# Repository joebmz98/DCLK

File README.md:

# DCLK — Dual MIDI Clock

**.axs instruments** · Firmware v1.6.3 · Hardware v1.0

DCLK is a dual MIDI clock built around an STM32F411 Black Pill. It sends
MIDI clock to two TRS (Type A) outputs and over USB MIDI, with quantised
start/stop and a separate clock divider for each output, so two machines can
be dropped in and out of a jam on the bar.

## Update the firmware

### ➜ [DCLK Web Flasher & Editor](https://joebmz98.github.io/DCLK-Flasher/)

Flash the latest release straight from Chrome or Edge on a computer. No
software to install. Your saved settings are kept. Flasher source:
[DCLK-Flasher](https://github.com/joebmz98/DCLK-Flasher).

1. Plug DCLK into the computer with a USB‑C data cable.
2. Put DCLK into update mode: click **Enter update mode** on the flasher,
   or choose **Settings > UPDATE** and push the encoder. The screen shows
   **DFU READY**. (Firmware 1.5 and later. On older firmware, or if DCLK
   won't start: hold **BOOT0**, tap **NRST**, keep holding BOOT0 for about a
   second. The screen and LEDs stay off in that mode.)
3. Click **Flash Firmware** and choose **STM32 BOOTLOADER**.

Windows needs a one-time WinUSB driver (Zadig); the flasher's Troubleshooting
section walks through it.

## Features

- Tempo from 30 to 300 BPM, set with the encoder (24 PPQN)
- Two TRS Type A MIDI outputs plus USB MIDI (class compliant, shows up as
  **DCLK**, no drivers)
- Quantised start: outputs wait for the next bar boundary of the wait length
  (1, 2, 4, 8 or 16 bars) before sending Start
- Optional quantised stop, landing on the same boundary
- Per-output clock divide: /1 /2 /3 /4 /6 /8
- USB MIDI clock follows either output
- Two 5 V analogue sync outputs (3.5 mm TRS): clock pulse on the tip
  (1, 2, 4, 8, 12 or 24 PPQN per output, default 24, after the channel's
  divider), run gate on the ring. SYNC 1 follows CH1, SYNC 2 follows CH2
  (firmware 1.6 and later; PPQN setting from 1.6.1)
- Screen saver: dims while a clock runs, switches off when stopped, with a
  slow breathing BEAT LED in standby
- Capacitive touch buttons (CAP1206) for CH1, CH2 and Settings
- Settings saved to flash and kept across power cycles and firmware updates

## Using DCLK

| Control | Action |
| --- | --- |
| Encoder (main screen) | Set tempo |
| **CH1** / **CH2** | Start or stop that output. Press again while waiting to cancel |
| **Settings** | Open the menu · back · cancel an edit |
| Encoder push | Select / confirm in the menu |

Clock, Start and Stop are MIDI System Real-Time messages, so they carry no
MIDI channel: "CH1" and "CH2" mean the two output jacks.

**LEDs**

- **CH1 / CH2:** solid while running, slow fade while waiting to start, blink
  on the beat while waiting for a quantised stop, off when stopped.
- **BEAT:** flashes on every beat.

**Main screen:** a white CH1 / CH2 tab appears along the top while that
output plays, and disappears when it stops (firmware 1.6.2 and later). Below them
are the tempo and four beat bars; the current beat stands taller. The bars
and the BEAT LED move while an output plays, and (from 1.6.3) while a USB
host plays in HOST mode even with both outputs off.

**Menus**

| Menu | Settings |
| --- | --- |
| LEDS | Brightness: LO / MID / HI |
| MIDI | WAIT LEN · STOP Q · CH1 DIV · CH2 DIV · USB OUT |
| SYNC | SYNC 1 / SYNC 2 pulses per quarter note: 1 / 2 / 4 / 8 / 12 / 24 |
| SCREEN | SAVER: OFF / 1 / 5 / 10 / 30 min |
| MONITOR | USB and clock diagnostics; encoder push toggles a USB test note (C4, ch 1) |
| UPDATE | Restart into DFU mode for the web flasher (push the encoder to confirm, SETTINGS cancels) |
| ABOUT | Product, maker and firmware version |

## Connections

| Connector | Use |
| --- | --- |
| USB‑C (Black Pill) | USB MIDI clock, power, firmware updates |
| MIDI OUT 1 / 2 | 3.5 mm TRS, Type A |
| SYNC OUT 1 / 2 | 3.5 mm TRS, 5 V: tip = clock pulse, ring = run gate (high while playing) |
| DC jack | 5 V, centre positive |

## Hardware

KiCad 9 project in `build/DCLK-MIDI-Clock/`, with JLCPCB-ready Gerbers,
BOM and placement files in `production/`. Custom footprints are in
`lib/DCLK.pretty/`.

Main parts: STM32F411CEU6 Black Pill, SSD1306 128×32 I²C OLED, CAP1206
touch controller, Alps EC11E encoder with switch, 2× CUI SJ1‑3525N TRS jacks,
GCT DCJ200 DC jack, 3× 5 mm LEDs.

| Function | Pin |
| --- | --- |
| MIDI OUT 1 / 2 (TX) | PA9 (USART1) / PA2 (USART2) |
| SYNC 1 clock / run | PA8 / PB15 (via 74AHCT125 to 5 V) |
| SYNC 2 clock / run | PA5 / PA4 (via 74AHCT125 to 5 V) |
| CH1 / CH2 / Settings touch pads | CAP1206 CS1 / CS2 / CS3 (I²C 0x28) |
| CAP1206 ALERT# | PB12 |
| Encoder A / B / push | PB4 / PB5 / PB13 |
| LED CH1 / CH2 / BEAT | PB8 / PB9 / PA6 (PWM) |
| OLED + CAP1206 SDA / SCL | PB7 / PB6 |

## Building the firmware

The sketch is `src/dclk_midi_clock/dclk_midi_clock.ino` (Arduino IDE).

- **Core:** STM32duino with the custom board entry
  **DCLK Dual MIDI Clock**, which gives a clean 48 MHz USB clock from the
  Black Pill's 25 MHz crystal. The sketch warns at compile time if another
  board is selected.
- **Board options:** USB support *None* (TinyUSB provides USB) · U(S)ART
  support *Enabled (generic 'Serial')*.
- **Libraries:** Adafruit GFX, Adafruit SSD1306, Adafruit TinyUSB.
- **Upload method:** STM32CubeProgrammer (DFU or SWD). The image must be
  linked at `0x08000000`, with no HID or UF2 bootloader offset.

To publish a release, use **Sketch > Export Compiled Binary**, copy the
`.hex` into the flasher repo's `firmware/` folder and update its
`manifest.json`.

## Repository layout

```
src/dclk_midi_clock/   firmware sketch, compiled builds, font
legacy/                every firmware release (hex, bin, source)
build/DCLK-MIDI-Clock/ KiCad project and production files
lib/DCLK.pretty/       custom footprints
assets/                artwork (polarity marking)
```

## License

MIT. See [LICENSE](LICENSE). © 2026 .axs instruments

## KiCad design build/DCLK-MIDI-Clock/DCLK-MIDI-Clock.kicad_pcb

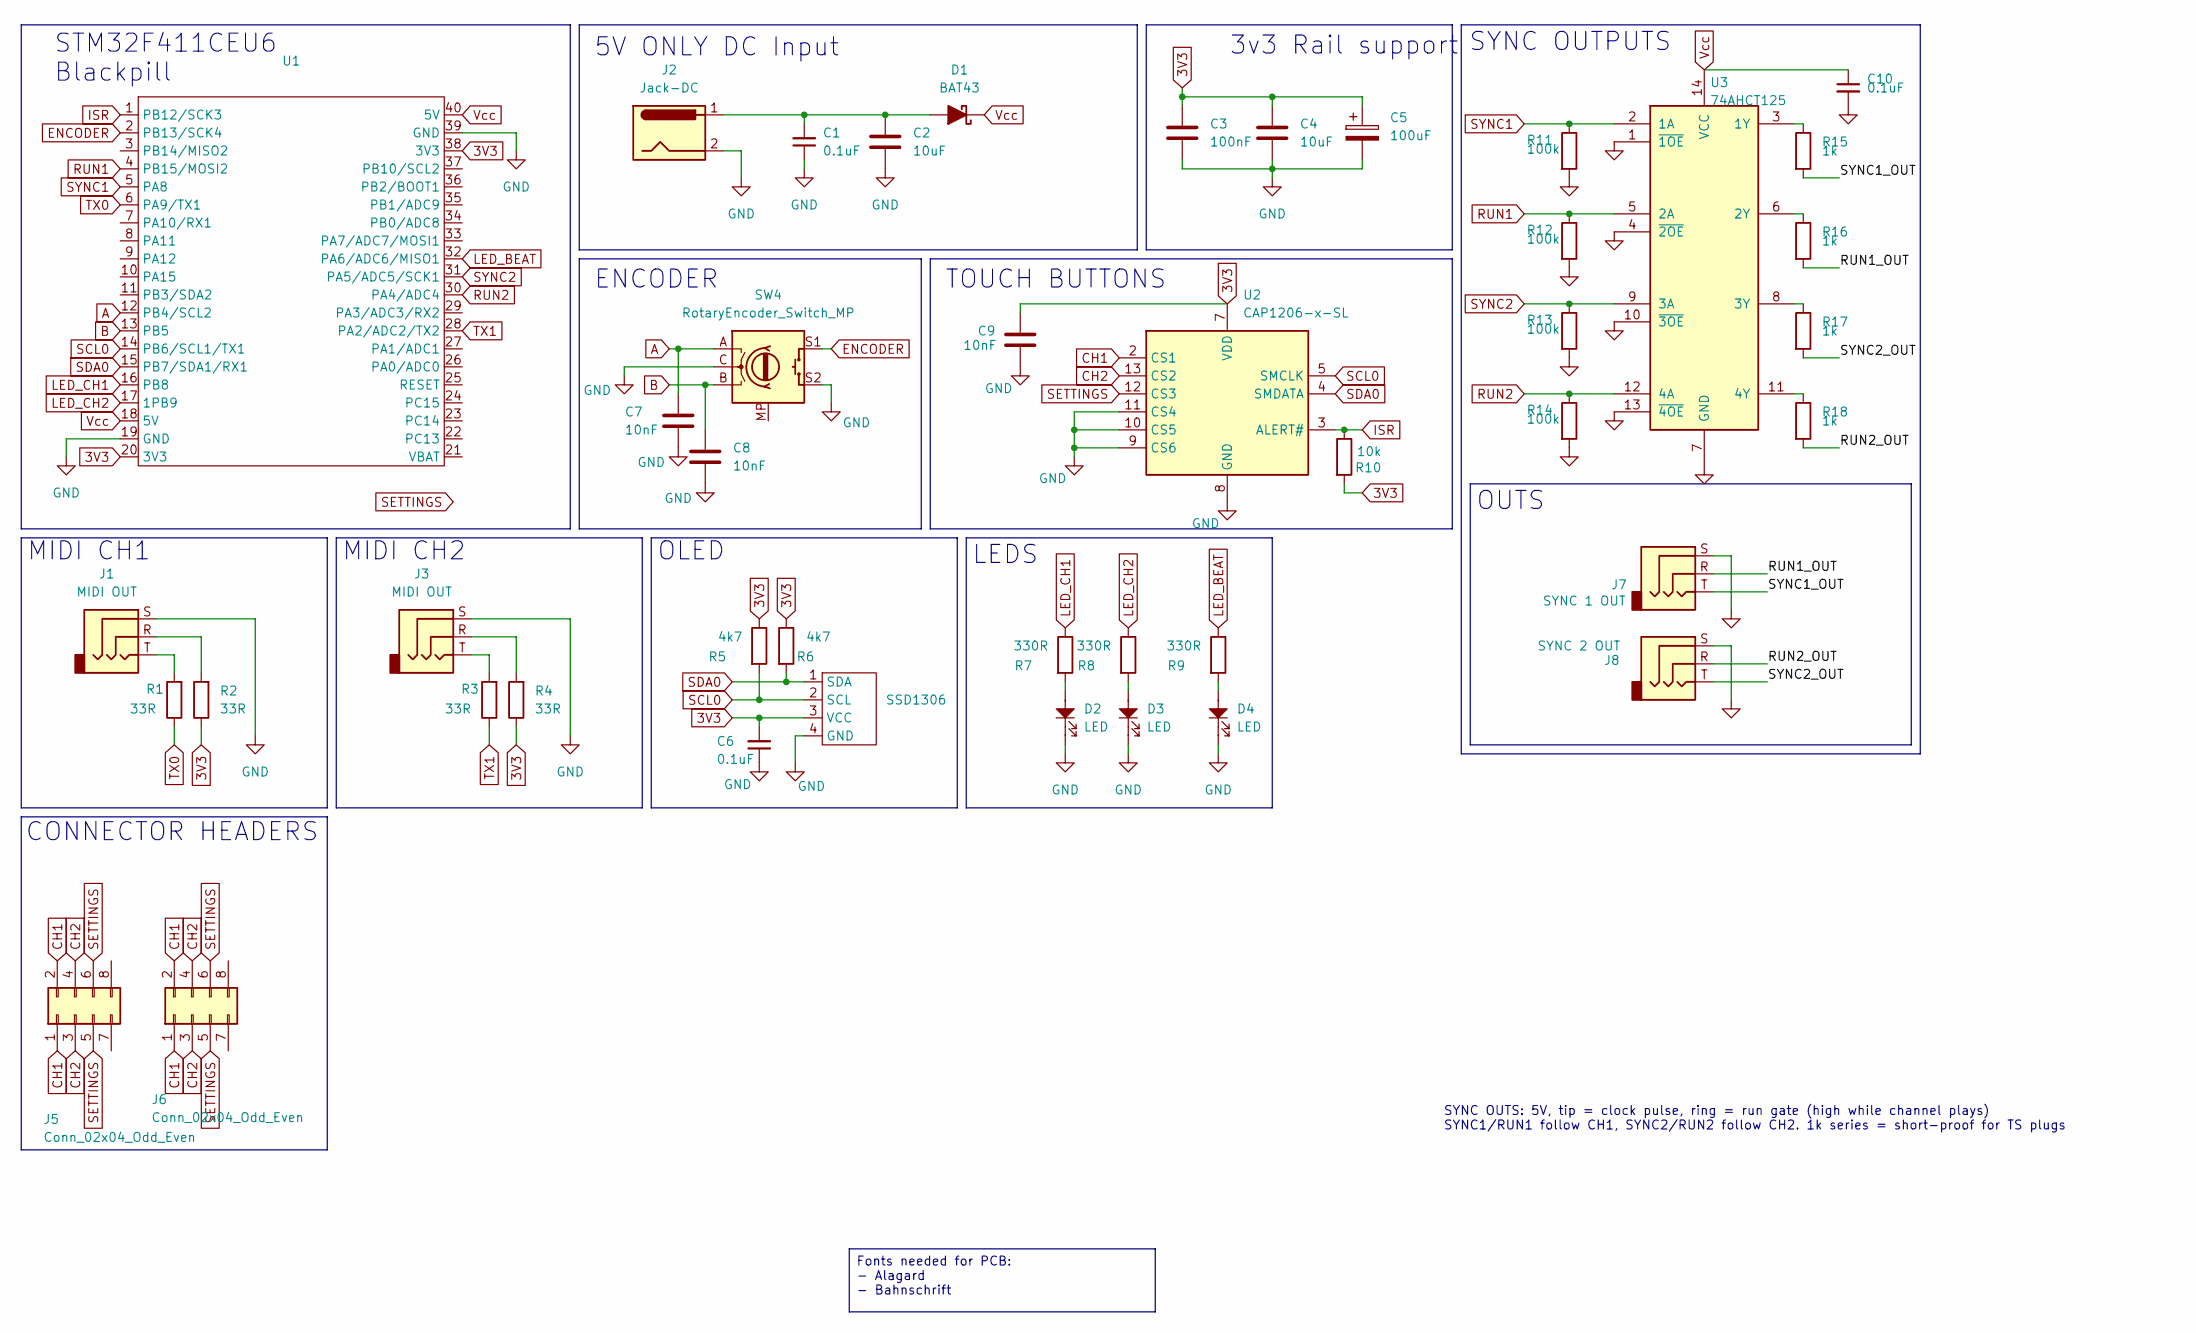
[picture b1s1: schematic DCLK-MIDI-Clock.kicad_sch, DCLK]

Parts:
C1, C6, C10: 100nF; C_1206_3216Metric; LCSC Part # C24497
C2, C4: 10uF; C_1206_3216Metric_Pad1.33x1.80mm_HandSolder; LCSC Part # C13585
C3: 100nF; C_1206_3216Metric_Pad1.33x1.80mm_HandSolder; LCSC Part # C24497
C5: 100uF; CP_Radial_D4.0mm_P1.50mm
C7, C8, C9: 10nF; C_1206_3216Metric_Pad1.33x1.80mm_HandSolder; LCSC Part # C1846
D1: BAT43; D_SOD-123; LCSC Part # C19167
D2, D3, D4: LED; LED_D5.0mm
J1, J3: MIDI OUT; Jack_3.5mm_CUI_SJ1-3525N_Horizontal_edit
J2: Jack-DC; BarrelJack_GCT_DCJ200-10-A_Horizontal
J5: Conn_02x04_Odd_Even; PinSocket_2x04_P2.54mm_Vertical; LCSC Part # C54907661
J6: Conn_02x04_Odd_Even; PinHeader_2x04_P2.54mm_Vertical_SMD; LCSC Part # C41397153
J7: SYNC 1 OUT; PJ307-TRS-SOCKET
J8: SYNC 2 OUT; PJ307-TRS-SOCKET
R1, R2, R3, R4: 33R; R_0603; LCSC Part # C23140
R5, R6: 4k7; R_0603; LCSC Part # C23162
R7, R8, R9: 330R; R_0603; LCSC Part # C22104
R10: 10k; R_0603; LCSC Part # C15401
R11, R12, R13, R14: 100k; R_0402_1005Metric; LCSC Part # C25530
R15, R16, R17, R18: 1k; R_0402_1005Metric; LCSC Part # C11702
SSD1306: SSD1306-128x32
SW4: RotaryEncoder_Switch_MP; RotaryEncoder_Alps_EC11E-Switch_Vertical_H20mm_MountingHoles
U1: Z_module_black_pill_STM32F411
U2: CAP1206-x-SL; SOIC-14_3.9x8.7mm_P1.27mm; LCSC Part # C2652106
U3: 74AHCT125; SOIC-14_3.9x8.7mm_P1.27mm; LCSC Part # C155176

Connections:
3V3: C3.1, C4.1, C5.1, C6.2, C9.2, R2.1, R4.1, R5.1, R6.1, R10.2, SSD1306.3 (VCC), U1.20 (3V3), U1.38 (3V3), U2.7 (VDD)
/RUN1_OUT: J7.R, R16.2
/RUN2_OUT: J8.R, R18.2
/SYNC1_OUT: J7.T, R15.2
/SYNC2_OUT: J8.T, R17.2
A: C7.1, SW4.A, U1.12 (PB4/SCL2)
B: C8.1, SW4.B, U1.13 (PB5)
CH1: J5.1, J5.2, J6.1, J6.2, U2.2 (CS1)
CH2: J5.3, J5.4, J6.3, J6.4, U2.13 (CS2)
ENCODER: SW4.S1, U1.2 (PB13/SCK4)
GND: C1.1, C2.2, C3.2, C4.2, C5.2, C6.1, C7.2, C8.2, C9.1, C10.2, D2.1, D3.1, D4.1, J1.S, J2.2, J3.S, J7.S, J8.S, R11.2, R12.2, R13.2, R14.2, SSD1306.4 (GND), SW4.C, SW4.S2, U1.19 (GND), U1.39 (GND), U2.8 (GND), U2.9 (CS6), U2.10 (CS5), U2.11 (CS4), U3.1 (~1OE), U3.4 (~2OE), U3.7 (GND), U3.10 (~3OE), U3.13 (~4OE)
ISR: R10.1, U1.1 (PB12/SCK3), U2.3 (ALERT#)
LED_BEAT: R9.1, U1.32 (PA6/ADC6/MISO1)
LED_CH1: R7.1, U1.16 (PB8)
LED_CH2: R8.1, U1.17 (1PB9)
unnamed: C1.2, C2.1, D1.2 (A), J2.1
unnamed: D2.2, R7.2
unnamed: D3.2, R8.2
unnamed: D4.2, R9.2
unnamed: J1.R, R2.2
unnamed: J1.T, R1.2
unnamed: J3.R, R4.2
unnamed: J3.T, R3.2
unnamed: R15.1, U3.3 (1Y)
unnamed: R16.1, U3.6 (2Y)
unnamed: R17.1, U3.8 (3Y)
unnamed: R18.1, U3.11 (4Y)
RUN1: R12.1, U1.4 (PB15/MOSI2), U3.5 (2A)
RUN2: R14.1, U1.30 (PA4/ADC4), U3.12 (4A)
SCL0: R5.2, SSD1306.2 (SCL), U1.14 (PB6/SCL1/TX1), U2.5 (SMCLK)
SDA0: R6.2, SSD1306.1 (SDA), U1.15 (PB7/SDA1/RX1), U2.4 (SMDATA)
SETTINGS: J5.5, J5.6, J6.5, J6.6, U2.12 (CS3)
SYNC1: R11.1, U1.5 (PA8), U3.2 (1A)
SYNC2: R13.1, U1.31 (PA5/ADC5/SCK1), U3.9 (3A)
TX0: R1.1, U1.6 (PA9/TX1)
TX1: R3.1, U1.28 (PA2/ADC2/TX2)
Vcc: C10.1, D1.1 (K), U1.18 (5V), U1.40 (5V), U3.14 (VCC)

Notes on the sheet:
SYNC OUTS: 5V, tip = clock pulse, ring = run gate (high while channel plays) SYNC1/RUN1 follow CH1, SYNC2/RUN2 follow CH2. 1k series = short-proof for TS plugs
OUTS
STM32F411CEU6 Blackpill
5V ONLY DC Input
TOUCH BUTTONS
3v3 Rail support
ENCODER
MIDI CH2
SYNC OUTPUTS
LEDS
MIDI CH1
CONNECTOR HEADERS
OLED
Fonts needed for PCB: - Alagard - Bahnschrift

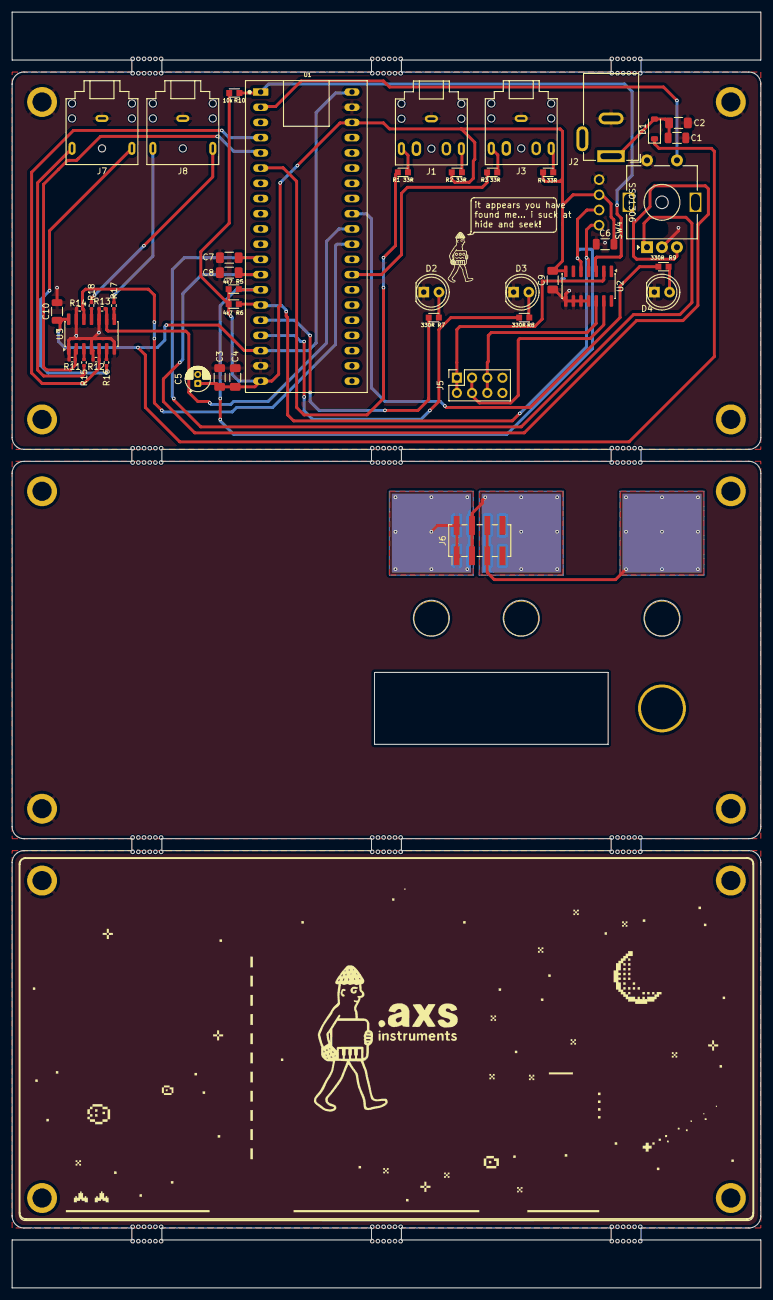
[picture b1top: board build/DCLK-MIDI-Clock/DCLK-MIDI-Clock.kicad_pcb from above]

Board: 2 copper layers, 125.0 x 213.0 mm, 56 parts (0 on the bottom side), 37 nets.

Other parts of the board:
MB**: MouseBite_Tab; MouseBite_Tab_5mm_Gap2mm
MB**#2, MB**#3, MB**#4, MB**#5, MB**#6, MB**#7, MB**#8, MB**#9, MB**#10, MB**#11, MB**#12: MouseBite_Tab; MouseBite_Tab_5mm_Gap2mm

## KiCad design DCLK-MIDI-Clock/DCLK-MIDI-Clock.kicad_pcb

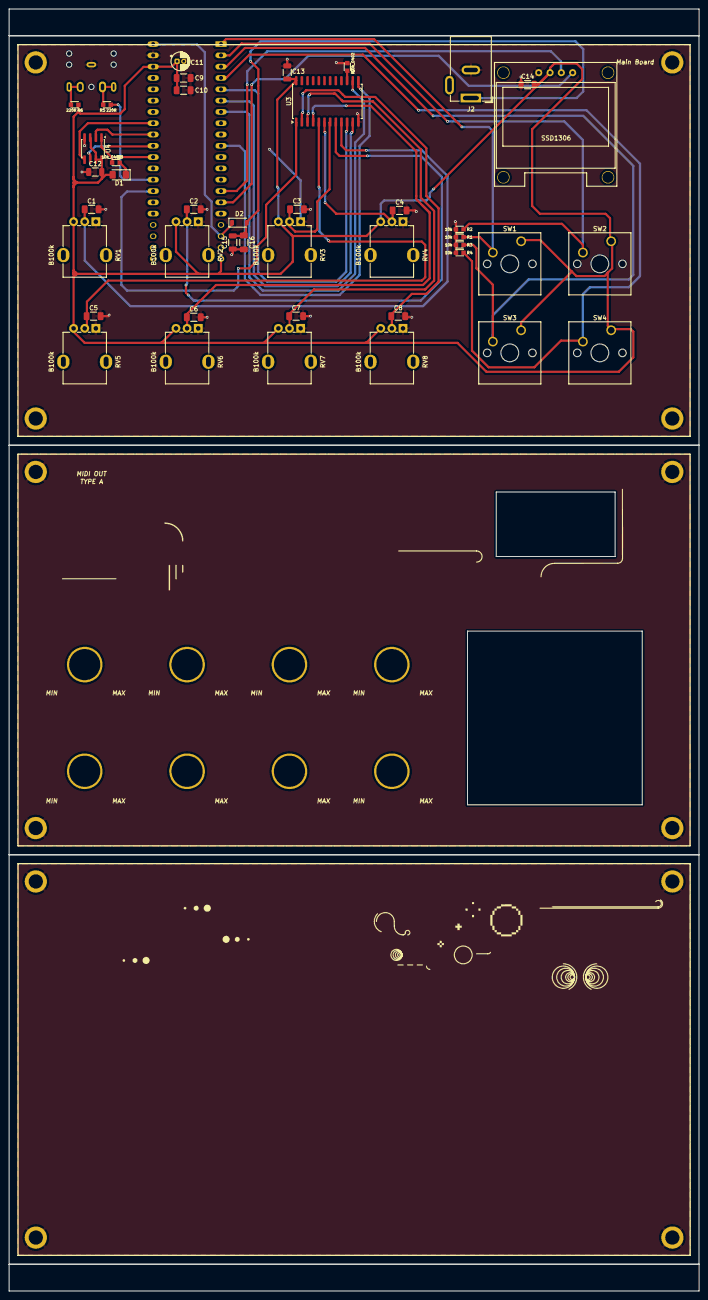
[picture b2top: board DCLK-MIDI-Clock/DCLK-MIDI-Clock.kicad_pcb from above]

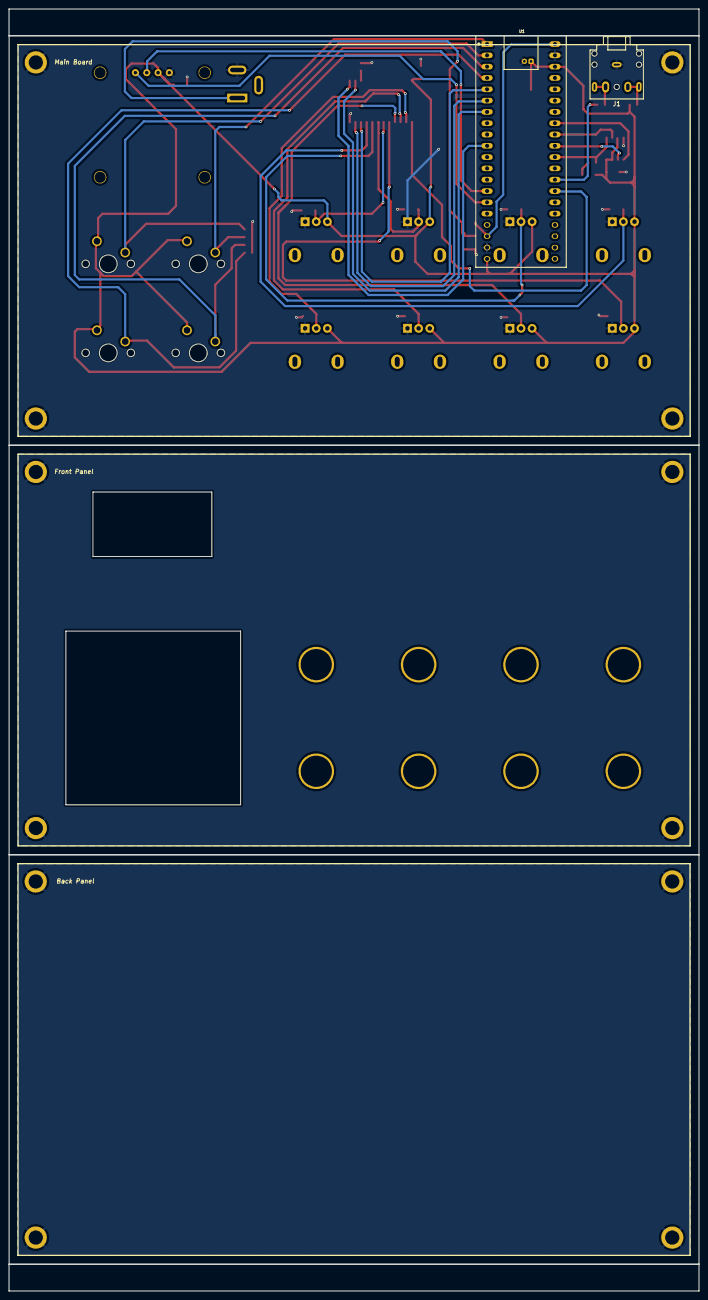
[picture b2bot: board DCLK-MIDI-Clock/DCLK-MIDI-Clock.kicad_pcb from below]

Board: 2 copper layers, 155.0 x 288.0 mm, 44 parts (3 on the bottom side), 32 nets.

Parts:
C1, C2, C3, C4, C5, C6, C7, C8: C_Generic; C_1206_3216Metric_Pad1.33x1.80mm_HandSolder
C9: 100nF; C_1206_3216Metric_Pad1.33x1.80mm_HandSolder
C10, C16: 10uF; C_1206_3216Metric_Pad1.33x1.80mm_HandSolder
C11: 100uF; CP_Radial_D4.0mm_P1.50mm
C12, C13, C14, C15: 100nF_0603_16V; C_1206_3216Metric
D1: LED; LED_1206_3216Metric_Pad1.42x1.75mm_HandSolder
D2: BAT43; D_SOD-123
J1: MIDI OUT; Jack_3.5mm_CUI_SJ1-3525N_Horizontal_edit
J2: Jack-DC; BarrelJack_GCT_DCJ200-10-A_Horizontal
R1, R2, R3, R4: 10k; R_0603
R5, R6: 220R; R_0603
R7, R8: 10k_0402; R_0603
RV1, RV2, RV3, RV4, RV5, RV6, RV7, RV8: B100k; Potentiometer_RV09_BigPads
SSD1306: SSD1306_OLED_Module
SW1: ASSIGN; SW_Cherry_MX_1.00u_PCB
SW2: ENTER; SW_Cherry_MX_1.00u_PCB
SW3: PREV; SW_Cherry_MX_1.00u_PCB
SW4: NEXT; SW_Cherry_MX_1.00u_PCB
U1: Z_module_black_pill_STM32F411
U3: CD74HC4067M; SOIC-24W_7.5x15.4mm_P1.27mm
U4: W25Q64; SOIC-8_3.9x4.9mm_P1.27mm

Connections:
3V3: C9.1, C10.1, C11.1, C12.2, C13.1, C14.2, D1.2 (A), R6.1, RV1.3, RV2.3, RV3.3, RV4.3, RV5.3, RV6.3, RV7.3, RV8.3, SSD1306.3 (VCC), SW1.1 (A), SW2.1 (A), SW3.1 (A), SW4.1 (A), U1.20 (3V3), U1.38 (3V3), U3.24 (VCC), U4.3 (WP), U4.7 (HOLD), U4.8 (VCC)
ASSIGN: R1.1, SW1.2 (B), U1.1 (PB12/SCK3)
CLK: U1.31 (PA5/ADC5/SCK1), U4.6 (CLK)
CS: R8.1, U1.30 (PA4/ADC4), U4.1 (CS)
ENTER: R2.1, SW2.2 (B), U1.2 (PB13/SCK4)
GND: C1.2, C2.2, C3.2, C4.2, C5.2, C6.2, C7.2, C8.2, C9.2, C10.2, C11.2, C12.1, C13.2, C14.1, C15.1, C16.2, J1.S, J2.2, R1.2, R2.2, R3.2, R4.2, R7.2, RV1.1, RV2.1, RV3.1, RV4.1, RV5.1, RV6.1, RV7.1, RV8.1, SSD1306.4 (GND), U1.19 (GND), U1.39 (GND), U3.12 (GND), U4.4 (GND)
MISO: U1.32 (PA6/ADC6/MISO1), U4.2 (MISO/DO)
MOSI: U1.33 (PA7/ADC7/MOSI1), U4.5 (MOSI/DI)
NEXT: R4.1, SW4.2 (B), U1.4 (PB15/MOSI2)
unnamed: D1.1 (K), R8.2
unnamed: C15.2, C16.1, D2.2 (A), J2.1
unnamed: J1.R, R6.2
unnamed: J1.T, R5.2
unnamed: R7.1, U3.15 (~E)
PREV: R3.1, SW3.2 (B), U1.3 (PB14/MISO2)
S0: U1.5 (PA8), U3.10 (S0)
S1: U1.6 (PA9/TX1), U3.11 (S1)
S2: U1.7 (PA10/RX1), U3.14 (S2)
S3: U1.10 (PA15), U3.13 (S3)
SCL0: SSD1306.2 (SCL), U1.14 (PB6/SCL1/TX1)
SDA0: SSD1306.1 (SDA), U1.15 (PB7/SDA1/RX1)
SIG: U1.27 (PA1/ADC1), U3.1 (COM)
TX0: R5.1, U1.28 (PA2/ADC2/TX2)
Vcc: D2.1 (K), U1.18 (5V), U1.40 (5V)
pot1: C1.1, RV1.2, U3.9 (I0)
pot2: C2.1, RV2.2, U3.8 (I1)
pot3: C3.1, RV3.2, U3.7 (I2)
pot4: C4.1, RV4.2, U3.6 (I3)
pot5: C5.1, RV5.2, U3.5 (I4)
pot6: C6.1, RV6.2, U3.4 (I5)
pot7: C7.1, RV7.2, U3.3 (I6)
pot8: C8.1, RV8.2, U3.2 (I7)

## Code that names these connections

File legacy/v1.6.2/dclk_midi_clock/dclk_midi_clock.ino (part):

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//
// CH1, CH2 and SETTINGS are capacitive touch pads read by a CAP1206
// (CS1 = CH1, CS2 = CH2, CS3 = SETTINGS) on the same I2C bus as the OLED,
// with its ALERT# line on PB12. The encoder and its push switch are wired
// straight to the BlackPill (PB4 / PB5 / PB13).
//
// SYNC OUTPUTS (v1.6+): two 3.5 mm TRS jacks, buffered to 5 V by a 74AHCT125.
//   Tip  = clock pulse, SYNC n PPQN setting per quarter note (after the
//          channel's clock divider), SYNC_PULSE_US wide
//   Ring = run gate, high while that channel is playing
//   SYNC 1 follows CH1 (PA8 tip, PB15 ring), SYNC 2 follows CH2 (PA5 tip,
//   PA4 ring). Pulse ends are timed by TIM5.
// ********************* //

// ********************* //
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constexpr uint8_t N_LED_LEVELS = sizeof(led_levels) / sizeof(led_levels[0]);

// ---------- Pins ----------
constexpr uint8_t PIN_ENC_A = PB4, PIN_ENC_B = PB5;
constexpr int8_t  ENC_DIR     = -1;         // +1 / -1: flips the encoder's direction everywhere
constexpr uint8_t PIN_ENC_BTN = PB13;       // encoder shaft push button
constexpr uint8_t PIN_TOUCH_ALERT = PB12;   // CAP1206 ALERT# (open drain, active low, R10 pull-up)

constexpr uint8_t PIN_LED_BEAT = PA6;                // TIM3_CH1 PWM
constexpr uint8_t PIN_LED_STATUS[2] = { PB8, PB9 };  // TIM4 PWM

HardwareSerial MidiOut1(PA10, PA9);  // USART1 (RX unused)
HardwareSerial MidiOut2(PA3, PA2);   // USART2 (RX unused)
HardwareSerial* midi[2] = { &MidiOut1, &MidiOut2 };

Adafruit_SSD1306 display(128, 32, &Wire, -1);
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volatile uint8_t usb_tx_tail = 0;

// Diagnostics (shown on the DIAG screen)
volatile uint32_t usb_ring_drops = 0;   // ISR found ring full
uint32_t usb_pkts_sent  = 0;            // packets accepted by TinyUSB
uint32_t usb_pkts_retry = 0;            // TinyUSB FIFO full, retried later

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  ABOUT
};
Screen  screen        = Screen::MAIN;
uint8_t menu_sel      = 0;     // SETTINGS: 0=LEDS 1=MIDI 2=SCREEN
uint8_t midi_menu_sel = 0;
uint8_t sync_menu_sel = 0;     // SYNC: 0 = SYNC 1, 1 = SYNC 2
uint8_t edit_idx      = 0;     // option index being edited (MIDI_EDIT / SAVER_EDIT)
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      display.fillRect(i * bar_w + 2, (i == b) ? 31 : 28, bar_w - 4, 4, SSD1306_WHITE);
    }
    display.display();
    analogWrite(PIN_LED_BEAT, b == 0 ? 255 : 140);
    delay(60);
    analogWrite(PIN_LED_BEAT, 0);
    delay(90);
  }

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}

void touchService() {
  static uint8_t  prev       = 0;
  static uint32_t last_poll  = 0;
  static uint32_t last_retry = 0;
  const uint32_t now = millis();
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    if (now - last_retry < TOUCH_RETRY_MS) return;
    last_retry = now;
    touch_ok = capInit();
    prev = 0;
    if (screen == Screen::DIAG) ui_dirty = true;
    return;
  }
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    return;
  }

  const uint8_t pressed = latched & TOUCH_MASK & ~prev;
  prev = current & TOUCH_MASK;

  if (pressed & TOUCH_CH1)      onOutputButton(0);
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    uint16_t peak = (uint16_t)led_base + led_flash;
    if (peak > 255) peak = 255;
    uint8_t beat_duty = (uint32_t)peak * (PPQN - 1 - phase) / (PPQN - 1);
    analogWrite(PIN_LED_BEAT, beat_duty);
  } else if (screen_asleep && !pending[0] && !pending[1]) {
    // Standby: soft breathe, one cycle per bar at the current tempo
    uint32_t period = 240000UL / bpm;                 // 4 beats in ms
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    uint32_t tri    = (pt < half) ? (pt * 255 / half) : ((period - pt) * 255 / half);
    uint16_t peak   = led_base / 3;
    if (peak < 8) peak = 8;                           // still visible at low LED setting
    analogWrite(PIN_LED_BEAT, (uint8_t)(((tri * tri) / 255) * peak / 255));
  } else {
    analogWrite(PIN_LED_BEAT, 0);
  }

  uint8_t flash = 0;
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  MidiOut1.flush();
  MidiOut2.flush();

  analogWrite(PIN_LED_BEAT,      0);
  analogWrite(PIN_LED_STATUS[0], 0);
  analogWrite(PIN_LED_STATUS[1], 0);

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    NVIC->ICPR[i] = 0xFFFFFFFF;
  }

  // PA10 is USART1_RX, which the bootloader also listens on. MIDI OUT 1
  // leaves it unconnected, and noise there can make the bootloader choose
  // the serial port instead of USB. Hold it high with the internal pull-up.
  __HAL_RCC_GPIOA_CLK_ENABLE();
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    digitalWriteFast(RUN_PIN[i],  LOW);
  }

  pinMode(PIN_LED_BEAT, OUTPUT);
  pinMode(PIN_LED_STATUS[0], OUTPUT);
  pinMode(PIN_LED_STATUS[1], OUTPUT);
  analogWriteFrequency(1000);
  analogWrite(PIN_LED_BEAT, 0);
  analogWrite(PIN_LED_STATUS[0], 0);
  analogWrite(PIN_LED_STATUS[1], 0);

  Wire.setSDA(PB7);
  Wire.setSCL(PB6);
  Wire.begin();
  Wire.setClock(400000);
  display.begin(SSD1306_SWITCHCAPVCC, 0x3C);
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  if (save_pending && usb_out_req < 0 && idle && !disp_busy) {
    save_pending = false;

    analogWrite(PIN_LED_BEAT,      0);
    analogWrite(PIN_LED_STATUS[0], 0);
    analogWrite(PIN_LED_STATUS[1], 0);

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

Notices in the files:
legacy/v1.6.2/dclk_midi_clock/dclk_midi_clock.ino:
This project is released under the MIT License.
Copyright (c) 2026 .axs instruments
